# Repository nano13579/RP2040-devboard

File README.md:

# an rp2040 dev board

This is a dev board based upon the RP2040 microcontroller, a 32-bit dual-core ARM Cortex-M0+. This board comes with 16mb of flash memory, a 12 MHz crystal oscillator, a USB-C for power with a Low-Dropout Regulator, and light sensing capabilites enabled using a TSL25911FN. I made this because I was interested in the use of various components for general RP2040 based boards. This was also my first time making a microcontoller in general, and I learned much about the purpose of various IC's and passive components in the process! 

| Item | Quantity | Product Link | Cost |
|------|----------|--------------|------|
| 1uF 0402 Cap | 2 | [link](https://jlcpcb.com/partdetail/SamsungElectro-CL05A105KA5NQNC/C52923) | $0.01 |
| 0.1uF 0402 Cap | 12 | [link](https://jlcpcb.com/partdetail/SamsungElectro-CL05B104KO5NNNC/C1525) | $0.01 |
| 33pF 0402 Cap | 2 | [link](https://jlcpcb.com/partdetail/TaiyoYuden-EMK042CH330JCW/C783027) | $0.01 |
| 10uF 0603 Cap | 2 | [link](https://jlcpcb.com/partdetail/2043-CL10A106MQ8NNNC/C1691) | $0.01 |
| 4.7K 0402 Resistor | 2 | [link](https://jlcpcb.com/partdetail/26643-0402WGF4701TCE/C25900) | $0.01 |
| 1K 0402 Resistor | 2 | [link](https://jlcpcb.com/partdetail/YAGEO-RC0100JR071KL/C327020) | $0.01 |
| 27 0402 Resistor | 2 | [link](https://jlcpcb.com/partdetail/YAGEO-RC0100JR0727RL/C850592) | $0.01 |
| 5.1K 0402 Resistor | 2 | [link](https://jlcpcb.com/partdetail/TyoHM-RMC04025_1K1N/C325521) | $0.01 |
| 10K 0402 Resistor | 1 | [link](https://jlcpcb.com/partdetail/259835-0105WHF1002TDE/C270305) | $0.01 |
| MCP1700x-330xxTT | 1 | [link](https://jlcpcb.com/partdetail/MicrochipTech-MCP1700T_3302ETT/C39051) | $0.39 |
| RP2040 | 1 | [link](https://jlcpcb.com/partdetail/RaspberryPi-RP2040/C2040) | $0.92 |
| W25Q16JVZPIQ TR | 1 | [link](https://jlcpcb.com/partdetail/WinbondElec-W25Q16JVZPIQTR/C2456208) | $0.90 |
| TSL25911FN | 1 | [link](https://jlcpcb.com/partdetail/AMS-TSL25911FN/C176812) | $1.74 |
| 12 MHz Crystal | 1 | [link](https://jlcpcb.com/partdetail/SeikoEpson-X1G0044510028/C32540) | $0.80 |
| Conn_01x20 (Pin Header) | 2 | [link](https://jlcpcb.com/partdetail/51993-2_54_1_20PStraightpin/C50981) | $0.21 |
| Conn_01x03 (Pin Header) | 1 | [link](https://jlcpcb.com/partdetail/50265-2_54_13PPin/C49257) | $0.02 |
| USB-C Receptacle | 1 | [link](https://jlcpcb.com/partdetail/Korean_HropartsElec-TYPE_C_31_M12/C165948) | $0.17 |
| Switch | 1 | [link](https://jlcpcb.com/partdetail/CK-KMR241GLFS/C221682) | $0.81 |

Total Parts Cost + PCBA + JLC Shipping = $13.83 + $3.20 + $24.26 = ($33.51 + taxes + feeder fees)*

*no need for grant - paying everything out of pocket

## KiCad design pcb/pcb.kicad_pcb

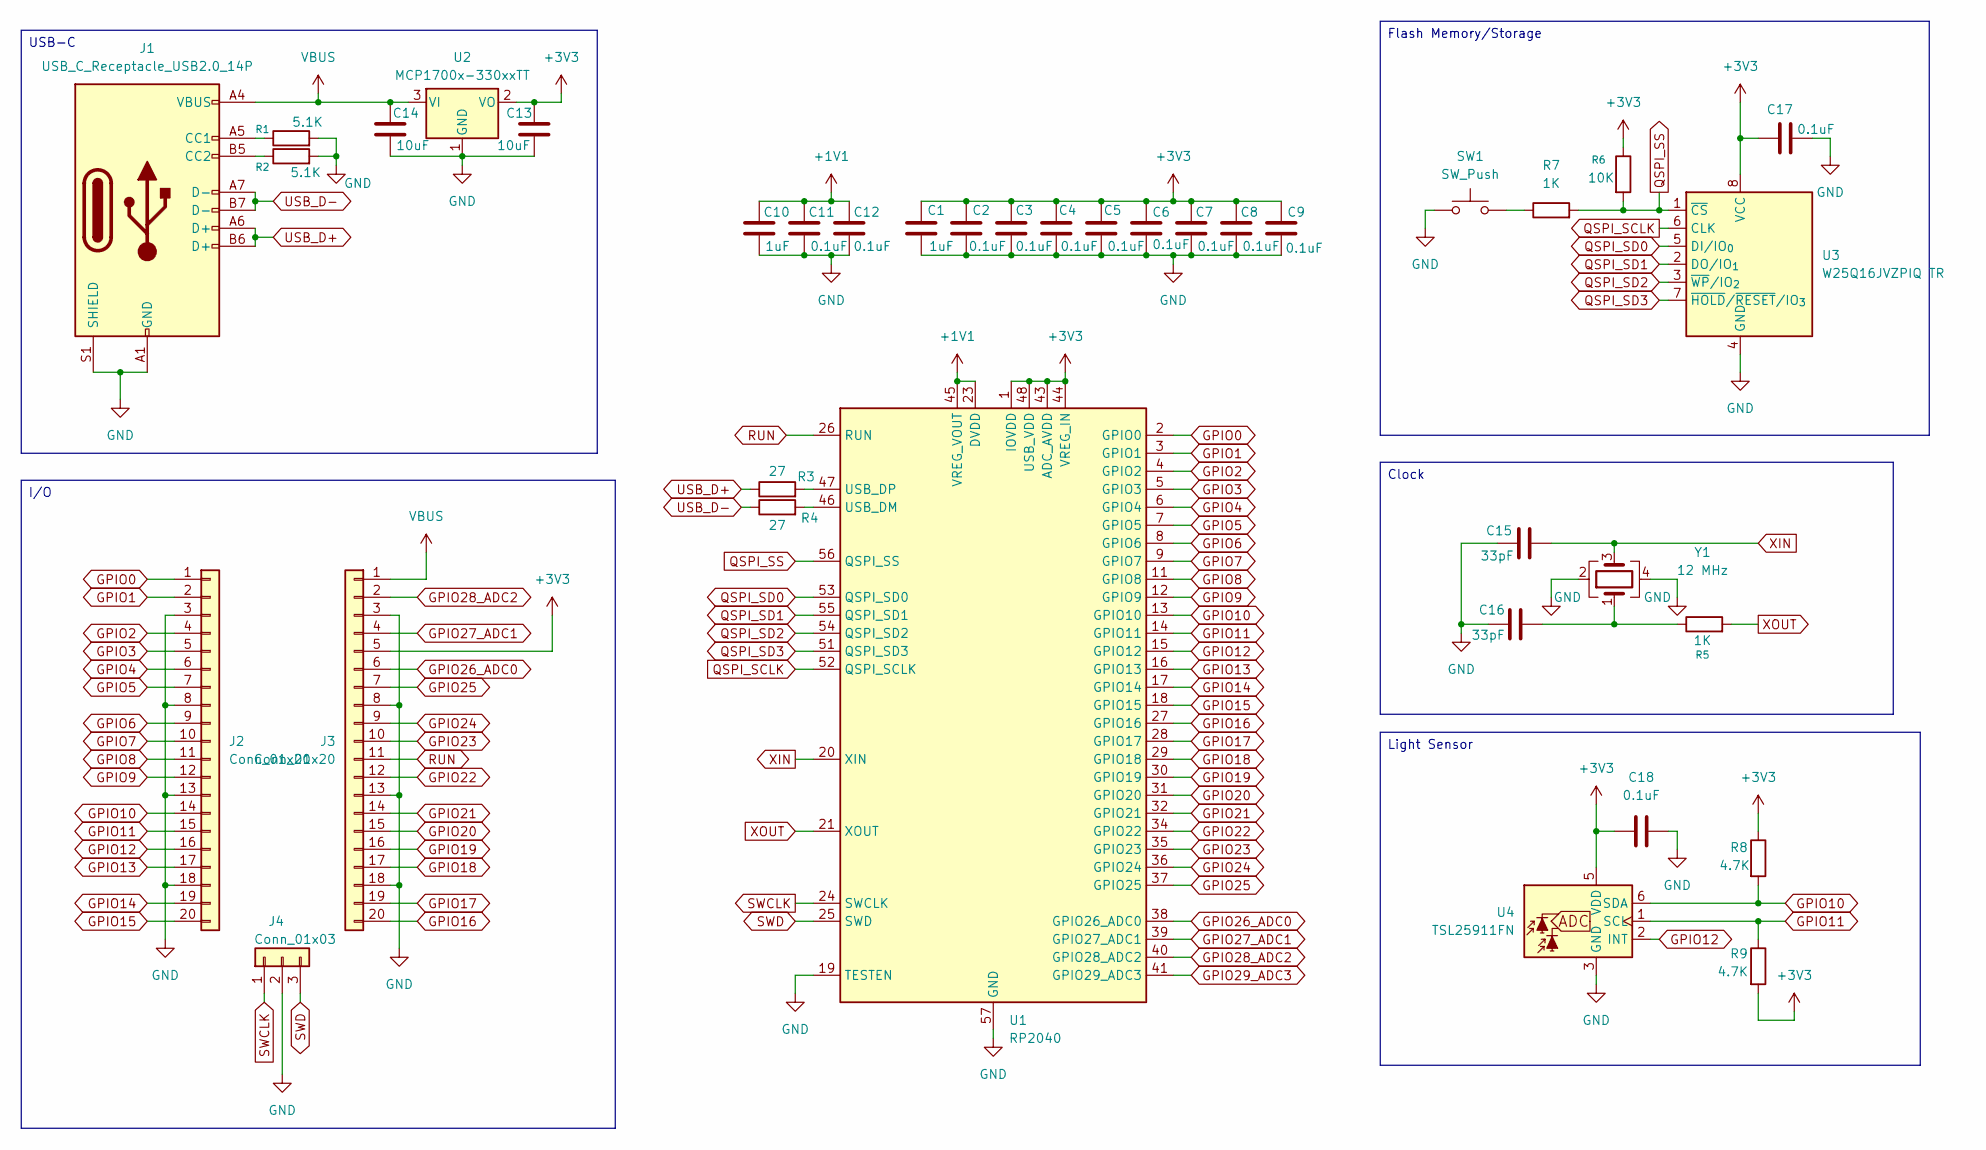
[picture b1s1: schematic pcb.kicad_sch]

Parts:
C1, C10: 1uF; C_01005_0402Metric
C2, C3, C4, C5, C6, C7, C8, C9, C11, C12, C17, C18: 0.1uF; C_01005_0402Metric
C13, C14: 10uF; C_0603_1608Metric
C15, C16: 33pF; C_01005_0402Metric
J1: USB_C_Receptacle_USB2.0_14P; USB_C_Receptacle_HRO_TYPE-C-31-M-12
J2, J3: Conn_01x20; PinHeader_1x20_P2.54mm_Vertical
J4: Conn_01x03; PinHeader_1x03_P2.54mm_Vertical
R1, R2: 5.1K; R_0402_1005Metric
R3, R4: 27; R_0402_1005Metric
R5, R7: 1K; R_0402_1005Metric
R6: 10K; R_0402_1005Metric
R8, R9: 4.7K; R_0402_1005Metric
SW1: SW_Push; SW_Push_SPST_NO_Alps_SKRK
U1: RP2040; QFN-56-1EP_7x7mm_P0.4mm_EP3.2x3.2mm
U2: MCP1700x-330xxTT; SOT-23
U3: W25Q16JVZPIQ TR; IC_W25Q16JVUXIQ_TR
U4: TSL25911FN; AMS_TSL25911FN
Y1: 12 MHz; Crystal_SMD_3225-4Pin_3.2x2.5mm

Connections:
+1V1: C10.1, C11.1, C12.1, U1.23 (DVDD), U1.45 (VREG_VOUT), U1.50 (DVDD)
+3V3: C1.1, C2.1, C3.1, C4.1, C5.1, C6.1, C7.1, C8.1, C9.1, C13.1, C17.1, C18.2, J3.5, R6.1, R8.1, R9.2, U1.1 (IOVDD), U1.10 (IOVDD), U1.22 (IOVDD), U1.33 (IOVDD), U1.42 (IOVDD), U1.43 (ADC_AVDD), U1.44 (VREG_IN), U1.48 (USB_VDD), U1.49 (IOVDD), U2.2 (VO), U3.8 (VCC), U4.5 (VDD)
GND: C1.2, C2.2, C3.2, C4.2, C5.2, C6.2, C7.2, C8.2, C9.2, C10.2, C11.2, C12.2, C13.2, C14.2, C15.1, C16.1, C17.2, C18.1, J1.A1 (GND), J1.A12 (GND), J1.B1 (GND), J1.B12 (GND), J1.S1 (SHIELD), J2.3, J2.8, J2.13, J2.18, J3.3, J3.8, J3.13, J3.18, J4.2, R1.2, R2.2, SW1.1, U1.19 (TESTEN), U1.57 (GND), U2.1 (GND), U3.4 (GND), U4.3 (GND), Y1.2, Y1.4
GPIO0: J2.1, U1.2 (GPIO0)
GPIO1: J2.2, U1.3 (GPIO1)
GPIO2: J2.4, U1.4 (GPIO2)
GPIO3: J2.5, U1.5 (GPIO3)
GPIO4: J2.6, U1.6 (GPIO4)
GPIO5: J2.7, U1.7 (GPIO5)
GPIO6: J2.9, U1.8 (GPIO6)
GPIO7: J2.10, U1.9 (GPIO7)
GPIO8: J2.11, U1.11 (GPIO8)
GPIO9: J2.12, U1.12 (GPIO9)
GPIO10: J2.14, R8.2, U1.13 (GPIO10), U4.6 (SDA)
GPIO11: J2.15, R9.1, U1.14 (GPIO11), U4.1 (SCL)
GPIO12: J2.16, U1.15 (GPIO12), U4.2 (INT)
GPIO13: J2.17, U1.16 (GPIO13)
GPIO14: J2.19, U1.17 (GPIO14)
GPIO15: J2.20, U1.18 (GPIO15)
GPIO16: J3.20, U1.27 (GPIO16)
GPIO17: J3.19, U1.28 (GPIO17)
GPIO18: J3.17, U1.29 (GPIO18)
GPIO19: J3.16, U1.30 (GPIO19)
GPIO20: J3.15, U1.31 (GPIO20)
GPIO21: J3.14, U1.32 (GPIO21)
GPIO22: J3.12, U1.34 (GPIO22)
GPIO23: J3.10, U1.35 (GPIO23)
GPIO24: J3.9, U1.36 (GPIO24)
GPIO25: J3.7, U1.37 (GPIO25)
GPIO26_ADC0: J3.6, U1.38 (GPIO26_ADC0)
GPIO27_ADC1: J3.4, U1.39 (GPIO27_ADC1)
GPIO28_ADC2: J3.2, U1.40 (GPIO28_ADC2)
GPIO29_ADC3: U1.41 (GPIO29_ADC3)
unnamed: C16.2, R5.1, Y1.1
unnamed: J1.A5 (CC1), R1.1
unnamed: J1.B5 (CC2), R2.1
unnamed: R7.1, SW1.2
unnamed: R4.2, U1.46 (USB_DM)
unnamed: R3.2, U1.47 (USB_DP)
QSPI_SCLK: U1.52 (QSPI_SCLK), U3.6 (CLK)
QSPI_SD0: U1.53 (QSPI_SD0), U3.5 (DI/IO_{0})
QSPI_SD1: U1.55 (QSPI_SD1), U3.2 (DO/IO_{1})
QSPI_SD2: U1.54 (QSPI_SD2), U3.3 (~WP/IO_{2})
QSPI_SD3: U1.51 (QSPI_SD3), U3.7 (~HOLD/~RESET/IO_{3})
QSPI_SS: R6.2, R7.2, U1.56 (QSPI_SS), U3.1 (~CS)
RUN: J3.11, U1.26 (RUN)
SWCLK: J4.1, U1.24 (SWCLK)
SWD: J4.3, U1.25 (SWD)
USB_D+: J1.A6 (D+), J1.B6 (D+), R3.1
USB_D-: J1.A7 (D-), J1.B7 (D-), R4.1
VBUS: C14.1, J1.A4 (VBUS), J1.A9 (VBUS), J1.B4 (VBUS), J1.B9 (VBUS), J3.1, U2.3 (VI)
XIN: C15.2, U1.20 (XIN), Y1.3
XOUT: R5.2, U1.21 (XOUT)

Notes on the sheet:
Clock
Light Sensor
USB-C
I/O
Flash Memory/Storage

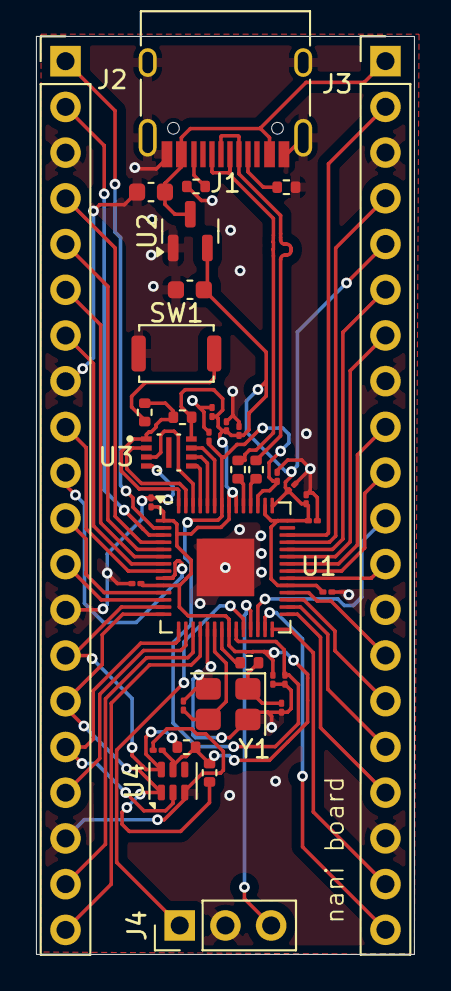
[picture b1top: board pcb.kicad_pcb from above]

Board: 2 copper layers, 21.0 x 51.0 mm, 37 parts (0 on the bottom side), 52 nets.

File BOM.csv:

Id,Designator,Footprint,Quantity,Comment,Supplier and ref
1,"C1,C10",C_01005_0402Metric,2,1uF,
2,"C2,C3,C4,C5,C6,C7,C8,C9,C11,C12,C17,C18",C_01005_0402Metric,12,0.1uF,
3,"C15,C16",C_01005_0402Metric,2,33pF,
4,J1,USB_C_Receptacle_HRO_TYPE-C-31-M-12,1,USB_C_Receptacle_USB2.0_14P,
5,"R8,R9",R_0402_1005Metric,2,4.7K,
6,U1,QFN-56-1EP_7x7mm_P0.4mm_EP3.2x3.2mm,1,RP2040,
7,U3,IC_W25Q16JVUXIQ_TR,1,W25Q16JVZPIQ TR,
8,U4,AMS_TSL25911FN,1,TSL25911FN,
9,"J2,J3",PinHeader_1x20_P2.54mm_Vertical,2,Conn_01x20,
10,J4,PinHeader_1x03_P2.54mm_Vertical,1,Conn_01x03,
11,"R7,R5",R_0402_1005Metric,2,1K,
12,"C13,C14",C_0603_1608Metric,2,10uF,
13,"R3,R4",R_0402_1005Metric,2,27,
14,"R2,R1",R_0402_1005Metric,2,5.1K,
15,SW1,SW_Push_SPST_NO_Alps_SKRK,1,SW_Push,
16,R6,R_0402_1005Metric,1,10K,
17,U2,SOT-23,1,MCP1700x-330xxTT,
18,Y1,Crystal_SMD_3225-4Pin_3.2x2.5mm,1,12 MHz,

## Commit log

2025-12-05 update schematic
2025-12-06 update pcb
2025-12-07 update pcb, readme, BOM
2025-12-07 update LDO price
2025-12-07 update README, silkscreen
